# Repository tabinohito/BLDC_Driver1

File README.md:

# BLDC_Driver1
## Review
- とりあえず回ったから、動作的に問題はなさそう
- でも、ACS758LCB-100U-PFF-Tの電流の測定範囲が -100 ~ 100 A で広すぎて分解能が辛い。
- ロックタイトで、ケーブル固定してるのは良き
- IRのゲートドライバが、アイソレートついてなくて辛い

## Parts List(肝心なとこだけ)
- 電流センサ : ACS758LCB-100U-PFF-T
- ゲートドライバ : IR2302
- FET : IRLB3813PBF
- DC-DC : M78AR12-0.5
- ヒートシンク : 幅24x高さ17x奥行25mm
- コネクタ 
  - PWM,CurrentSensor,HallSensor_Output : XHコネクタ　<br>
  - HallSensor_Input : ZHコネクタ <br>
  - Vin : XT60 <br>

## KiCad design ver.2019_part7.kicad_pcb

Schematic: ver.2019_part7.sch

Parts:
C1: 220uF; CP_Elec_10x7.9
C2, C3, C4, C5, C6: 3.3uF; C_1210_3225Metric
C7, C8, C9, C10, C11, C12, C13, C14, C15, C16, C17, C18: 0.1uF; C_0603_1608Metric
D1, D2, D3: D; D_SOD-123
J1: Vin; XT60Conector
J2: U; conecter_1
J3: V; conecter_1
J4: W; conecter_1
J5: Input_Signal; JST_XH_B08B-XH-A_1x08_P2.50mm_Vertical
J6: Current_Sensor; JST_XH_B04B-XH-A_1x04_P2.50mm_Vertical
J7: Hall_Sensor; JST_XH_B05B-XH-A_1x05_P2.50mm_Vertical
J8: Hall_input; SHDR6W50P0X150_1X6_1050X350X450P
MH1, MH2, MH3, MH4, MH5, MH6, MH7, MH8, MH9, MH10: MountingHole; MountingHole_3.2mm_M3
Q1, Q2, Q3, Q4, Q5, Q6: Q_NMOS_GDS; TO-220-3_Vertical
R1, R2, R3: 10k; R_0603_1608Metric
R4, R5, R6, R7, R8, R9: 330; R_0603_1608Metric
R10, R11, R12, R13, R14, R15: 20-100; R_0603_1608Metric
R16, R17, R18, R19, R20, R21: 220k; R_0603_1608Metric
U1, U2, U3, U4, U5, U6: TLP152; SO-6
U7, U8, U9: IR2108; DIP-8_W7.62mm
U10: L7812; SHDR3W75P0X254_1X3_1128X755X1070P
U11, U12, U13: ACS758xCB-100U-PFF; Allegro_CB_PFF
U14: Heatsink_U_H; SHDR2W140P0X1780_1X2_2350X1700X2500P; Manufacturer_Part_Number 17PB024-01025
U15: Heatsink_U_L; SHDR2W140P0X1780_1X2_2350X1700X2500P; Manufacturer_Part_Number 17PB024-01025
U16: Heatsink_V_H; SHDR2W140P0X1780_1X2_2350X1700X2500P; Manufacturer_Part_Number 17PB024-01025
U17: Heatsink_V_L; SHDR2W140P0X1780_1X2_2350X1700X2500P; Manufacturer_Part_Number 17PB024-01025
U18: Heatsink_W_H; SHDR2W140P0X1780_1X2_2350X1700X2500P; Manufacturer_Part_Number 17PB024-01025
U19: Heatsink_W_L; SHDR2W140P0X1780_1X2_2350X1700X2500P; Manufacturer_Part_Number 17PB024-01025

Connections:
+5VL: C16.1, C17.1, C18.1, J5.7, J7.4, J8.6, R1.2, R2.2, R3.2, U11.1 (VCC), U12.1 (VCC), U13.1 (VCC)
+12V: C6.1, C7.1, C8.1, C9.1, C10.1, C11.1, C12.1, C13.1, C14.1, C15.1, D1.2, D2.2, D3.2, U1.6, U2.6, U3.6, U4.6, U5.6, U6.6, U7.1 (VCC), U8.1 (VCC), U9.1 (VCC), U10.3 (OUT)
/U_ADC: J6.1, U11.3 (VIOUT)
/U_Current: Q6.3, R21.1, U11.4 (IP+)
/U_H: R14.2, U7.7 (HO)
/U_Hall: J7.1, J8.2, R3.1
/U_L: R15.2, U7.5 (LO)
/U_Out: C2.2, J2.1, Q5.3, Q6.2, R20.1, U7.6 (VS)
/V_ADC: J6.2, U12.3 (VIOUT)
/V_Current: Q4.3, R19.1, U12.4 (IP+)
/V_H: R12.2, U8.7 (HO)
/V_Hall: J7.2, J8.3, R2.1
/V_L: R13.2, U8.5 (LO)
/V_Out: C3.2, J3.1, Q3.3, Q4.2, R18.1, U8.6 (VS)
/W_ADC: J6.3, U13.3 (VIOUT)
/W_Current: Q2.3, R17.1, U13.4 (IP+)
/W_H: R10.2, U9.7 (HO)
/W_Hall: J7.3, J8.4, R1.1
/W_L: R11.2, U9.5 (LO)
/W_Out: C4.2, J4.1, Q1.3, Q2.2, R16.1, U9.6 (VS)
/input_U_H: J5.1, R4.2
/input_U_L: J5.2, R5.2
/input_V_H: J5.3, R6.2
/input_V_L: J5.4, R7.2
/input_W_H: J5.5, R8.2
/input_W_L: J5.6, R9.2
GND: C16.2, C17.2, C18.2, J5.8, J6.4, J7.5, J8.1, U1.3, U2.3, U3.3, U4.3, U5.3, U6.3, U11.2 (GND), U12.2 (GND), U13.2 (GND)
GNDPWR: C1.2, C5.2, C6.2, C7.2, C8.2, C9.2, C10.2, C11.2, C12.2, C13.2, C14.2, C15.2, J1.1, U1.4, U2.4, U3.4, U4.4, U5.4, U6.4, U7.4 (COM), U8.4 (COM), U9.4 (COM), U10.2 (GND), U11.5 (IP-), U12.5 (IP-), U13.5 (IP-)
unnamed: C2.1, D1.1, U7.8 (VB)
unnamed: C3.1, D2.1, U8.8 (VB)
unnamed: C4.1, D3.1, U9.8 (VB)
unnamed: Q1.1, R10.1, R16.2
unnamed: Q2.1, R11.1, R17.2
unnamed: Q3.1, R12.1, R18.2
unnamed: Q4.1, R13.1, R19.2
unnamed: Q5.1, R14.1, R20.2
unnamed: Q6.1, R15.1, R21.2
unnamed: R4.1, U1.1
unnamed: R5.1, U2.1
unnamed: R6.1, U3.1
unnamed: R7.1, U4.1
unnamed: R8.1, U5.1
unnamed: R9.1, U6.1
unnamed: U1.5, U7.2 (HIN)
unnamed: U2.5, U7.3 (~LIN)
unnamed: U3.5, U8.2 (HIN)
unnamed: U4.5, U8.3 (~LIN)
unnamed: U5.5, U9.2 (HIN)
unnamed: U6.5, U9.3 (~LIN)
VCC: C1.1, C5.1, J1.2, Q1.2, Q3.2, Q5.2, U10.1 (IN)

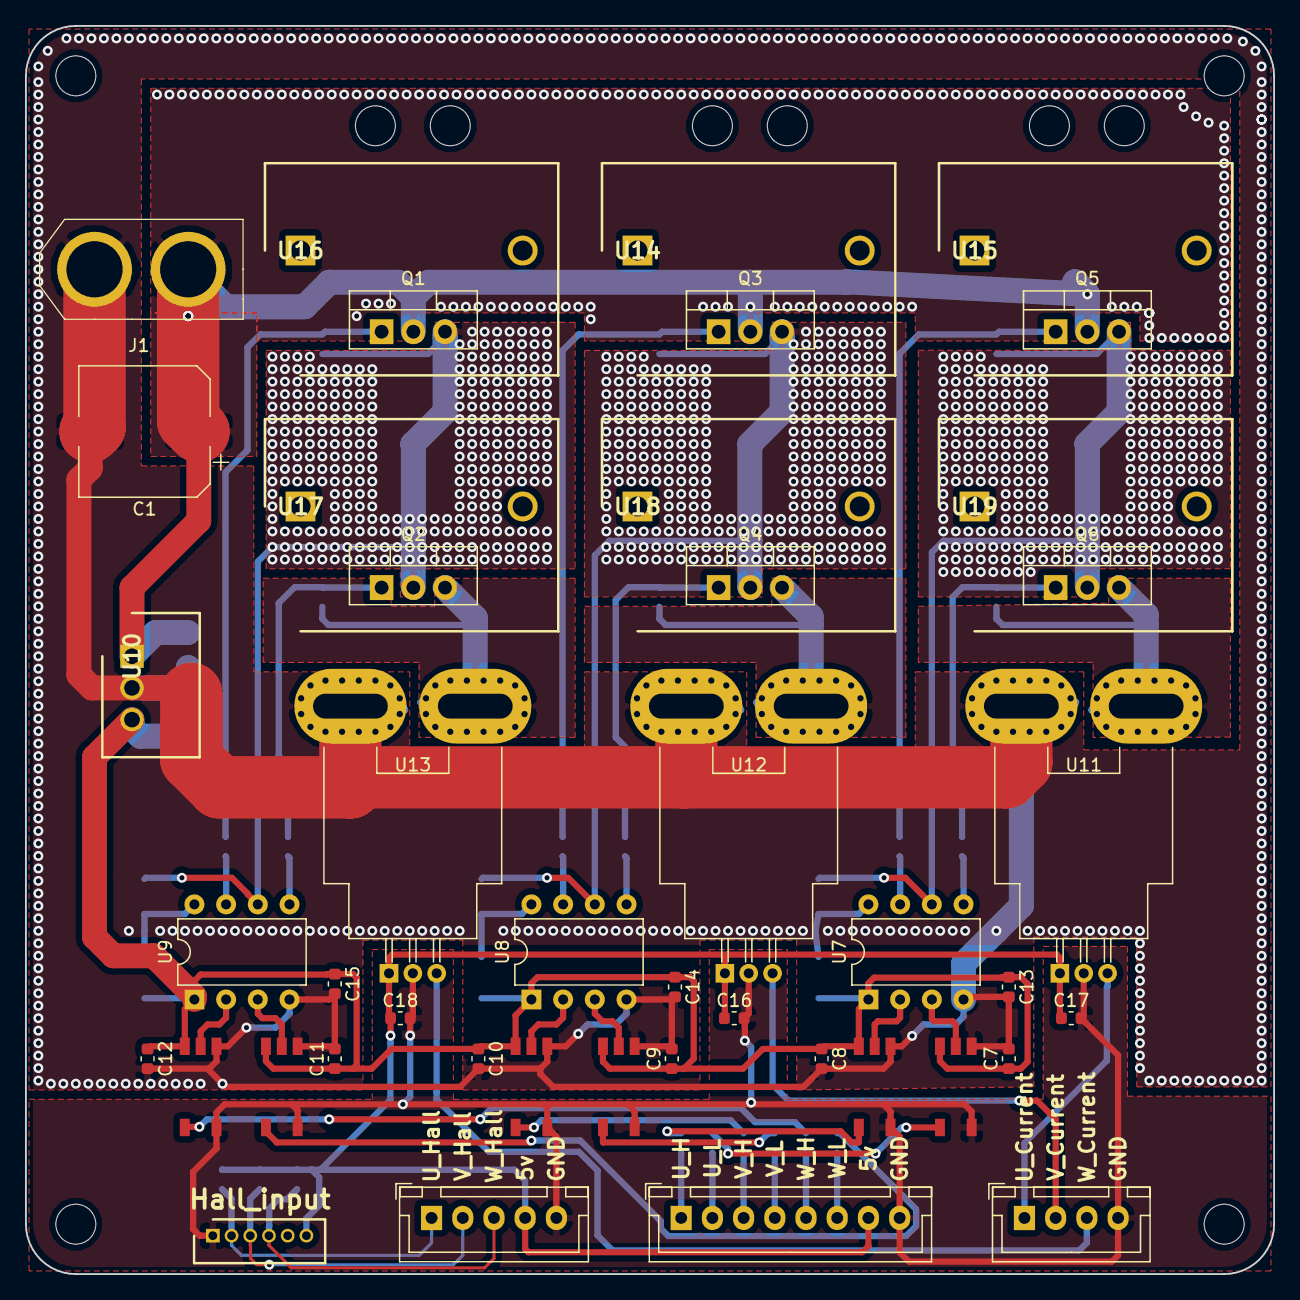
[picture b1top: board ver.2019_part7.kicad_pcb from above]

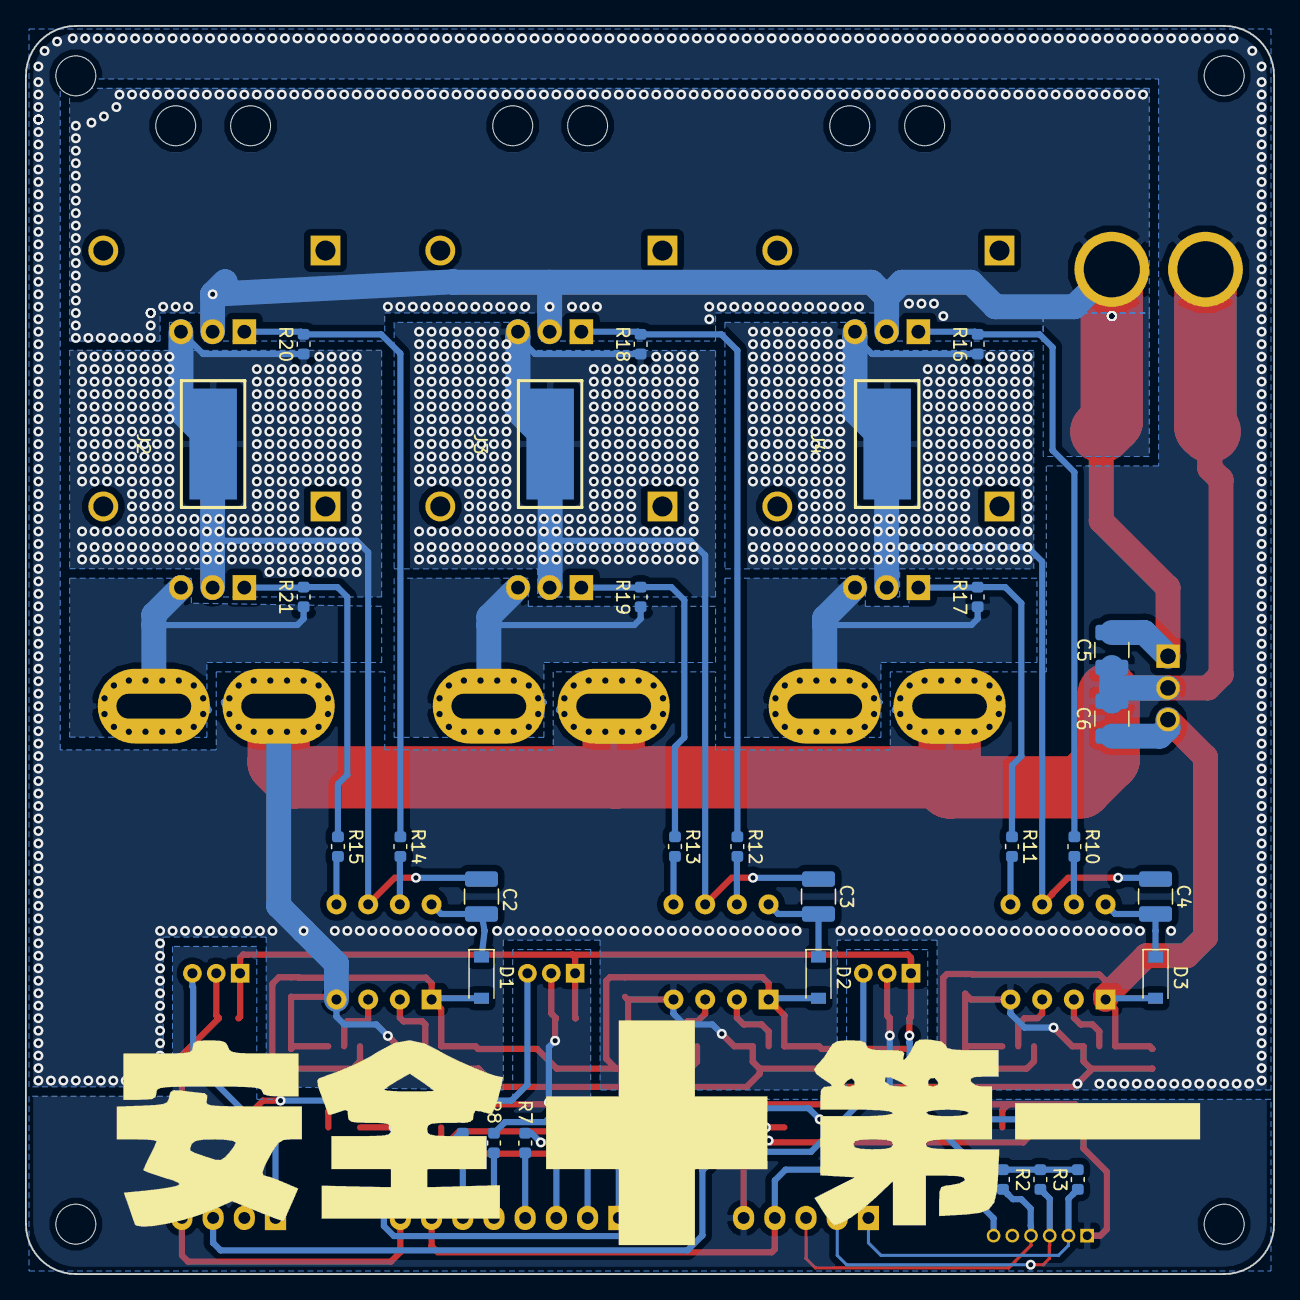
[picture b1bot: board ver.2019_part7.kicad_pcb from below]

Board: 2 copper layers, 100.0 x 100.0 mm, 85 parts (32 on the bottom side), 50 nets.

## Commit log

2020-07-03 Probably Complete
